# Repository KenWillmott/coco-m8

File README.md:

# coco-m8

This PCB interfaces M8 peripheral cards to the Tandy TRS-80 Color Computer

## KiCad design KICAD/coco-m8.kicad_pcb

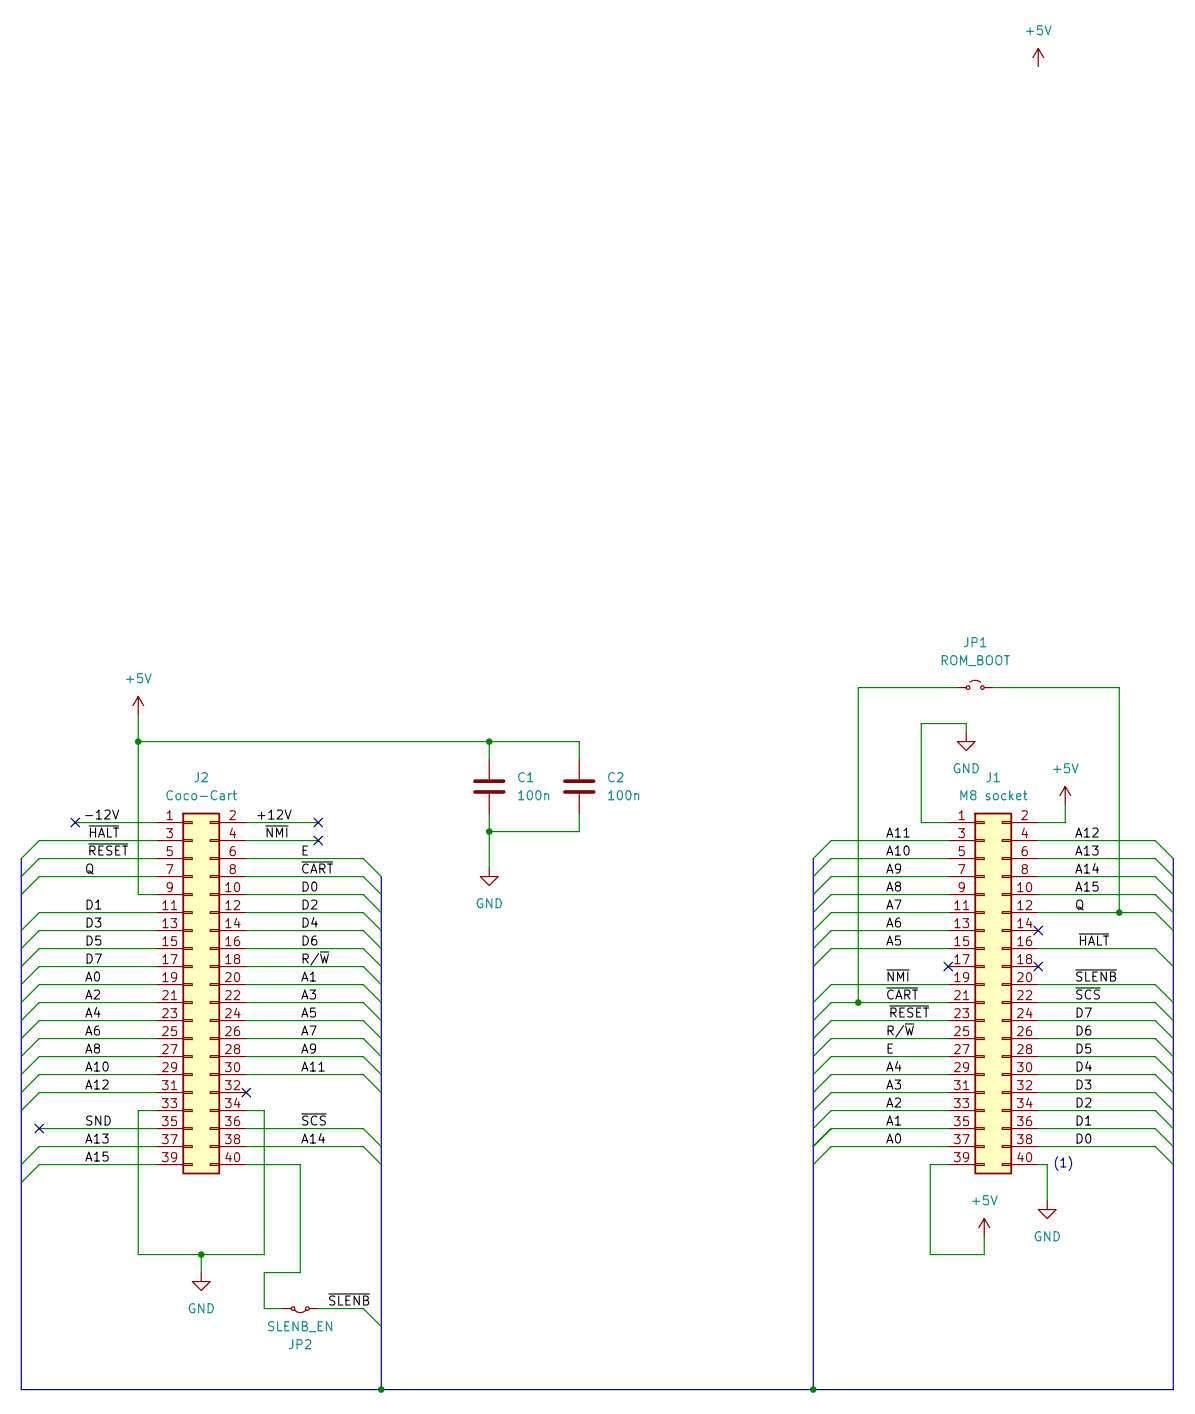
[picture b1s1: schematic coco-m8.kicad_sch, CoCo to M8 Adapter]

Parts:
C1, C2: 100n; C_Disc_D6.0mm_W2.5mm_P5.00mm
J1: M8 socket; PinSocket_2x20_P2.54mm_Horizontal
J2: Coco-Cart; Coco_Cart
JP1: ROM_BOOT; SolderJumper-2_P1.3mm_Open_RoundedPad1.0x1.5mm
JP2: SLENB_EN; SolderJumper-2_P1.3mm_Bridged_RoundedPad1.0x1.5mm

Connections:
+5V: C1.2, C2.1, J1.2, J1.39, J2.9
/+12V: J2.2
/-12V: J2.1
/A0: J1.37, J2.19
/A1: J1.35, J2.20
/A2: J1.33, J2.21
/A3: J1.31, J2.22
/A4: J1.29, J2.23
/A5: J1.15, J2.24
/A6: J1.13, J2.25
/A7: J1.11, J2.26
/A8: J1.9, J2.27
/A9: J1.7, J2.28
/A10: J1.5, J2.29
/A11: J1.3, J2.30
/A12: J1.4, J2.31
/A13: J1.6, J2.37
/A14: J1.8, J2.38
/A15: J1.10, J2.39
/D0: J1.38, J2.10
/D1: J1.36, J2.11
/D2: J1.34, J2.12
/D3: J1.32, J2.13
/D4: J1.30, J2.14
/D5: J1.28, J2.15
/D6: J1.26, J2.16
/D7: J1.24, J2.17
/E: J1.27, J2.6
/Q: J1.12, J2.7, JP1.2 (B)
/R/~W: J1.25, J2.18
/SND: J2.35
/~CART: J1.21, J2.8, JP1.1 (A)
/~HALT: J1.16, J2.3
/~NMI: J1.19, J2.4
/~RESET: J1.23, J2.5
/~SCS: J1.22, J2.36
/~SLENB: J1.20, JP2.2 (B)
GND: C1.1, C2.2, J1.1, J1.40, J2.33, J2.34
unnamed: J2.40, JP2.1 (A)

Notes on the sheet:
(1)

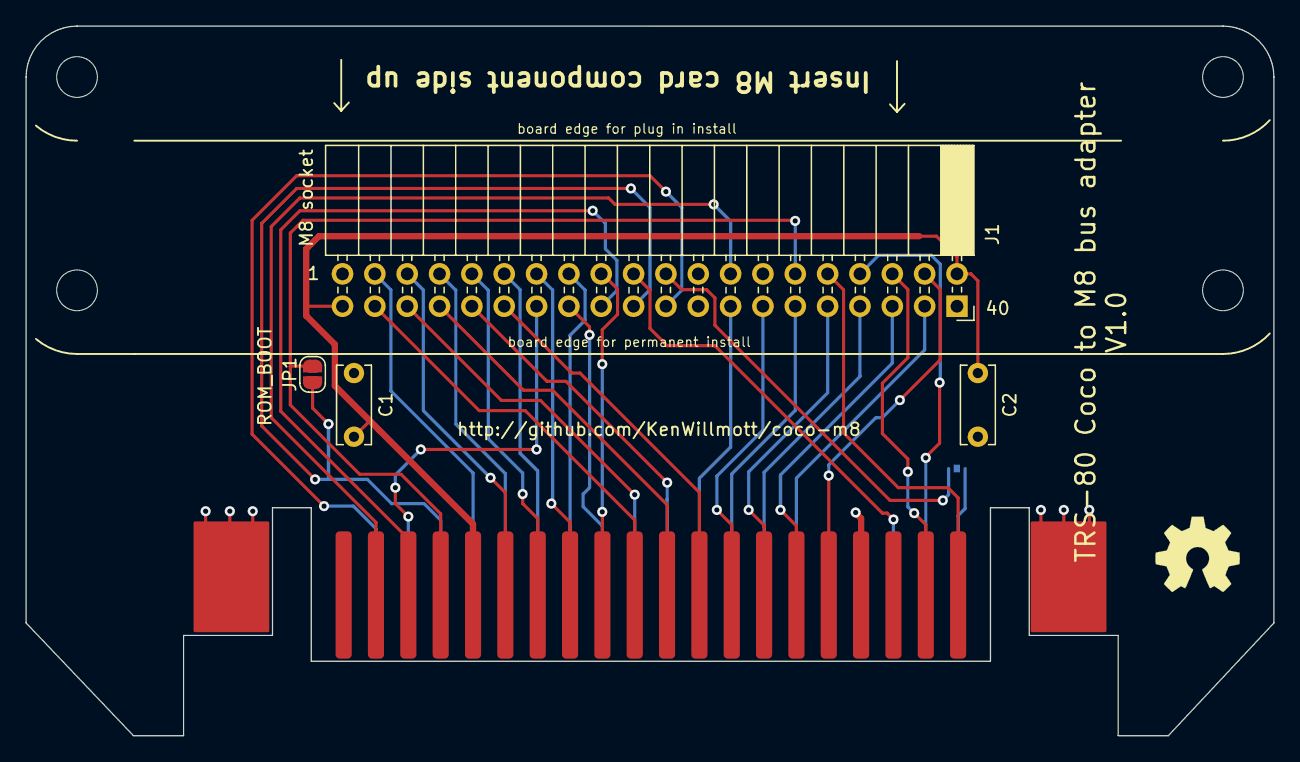
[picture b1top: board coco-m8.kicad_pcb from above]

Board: 2 copper layers, 98.0 x 55.7 mm, 6 parts (1 on the bottom side), 36 nets.
